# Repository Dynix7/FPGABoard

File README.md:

# FPGABoard
This is a FPGA (Field Programmable Array) board that consists of a iCE40 FPGA, FT2232 Programmer, and IO options. It has 2 PMOD headers (12 pin and 6 pin) along with an programming header and 26 pin header for anything else you want to plug in. On the board it has 3 LEDs and 3 buttons, allowing you to interact with the board without plugging anything in

# Why I Made It
I have a decent amount of experience working with microcontrollers but never any with FPGAs. I also want to learn Verilog which allows you to design circuits using programming, so a FPGA board would be perfect for this use case allowing me to experiment with Verilog and designing circuits while also learning something new.

# Pictures

# BOM

|Name                  |Purpose                        |Quantity|Total Cost (USD)|Link                                                                                                                       |Distributor|
|----------------------|-------------------------------|--------|----------------|---------------------------------------------------------------------------------------------------------------------------|-----------|
|6 Pin Header          |6 Pin PMOD Connector           |        |0.39            |https://www.lcsc.com/product-detail/C2935996.html                                                                          |LCSC       |
|2x6 Pin Header        |12 Pin PMOD Connector          |        |0.74            |https://www.lcsc.com/product-detail/C47326634.html                                                                         |LCSC       |
|2x4 Pin Header        |Programing Header              |        |0.52            |https://www.lcsc.com/product-detail/C7494793.html                                                                          |LCSC       |
|2x13 Pin Female Header|IO Pin Header                  |        |0.32            |https://www.lcsc.com/product-detail/C19268725.html                                                                         |LCSC       |
|Ferrite Bead 60@100   |Power Filtering                |        |0.23            |https://www.lcsc.com/product-detail/C307775.html                                                                           |LCSC       |
|Solder Paste          |Solder Components              |1       |4.79            |https://www.aliexpress.us/item/3256809026940371.html                                                                       |Aliexpress |
|4.7u Capacitors       |Decoupling Capacitors          |        |0.10            |                                                                                                                           |LCSC       |
|12k Resistor          |Resistor                       |        |0.11            |                                                                                                                           |LCSC       |
|2.2k Resistor         |Resistor                       |        |0.13            |                                                                                                                           |LCSC       |
|IS62LV256AL-45ULI     |SRAM for Chip                  |1       |1.84            |https://www.digikey.com/short/70fz9v3d                                                                                     |Digikey    |
|12Mhz Oscillator      |Clock for FPGA and FT2232      |2       |0.87            |https://www.lcsc.com/product-detail/C37635404.html                                                                         |LCSC       |
|93LC66BT-I/OT         |FT2232 Memory                  |        |0.35            |https://www.digikey.com/short/q0nprmz5                                                                                     |Digikey    |
|AP2127K-1.2           |1.2V Voltage Regulator         |        |0.59            |https://www.lcsc.com/product-detail/C151376.html                                                                           |LCSC       |
|AP2127K-3.3           |3.3V Voltage Regulator         |        |0.53            |https://www.lcsc.com/product-detail/C156285.html                                                                           |LCSC       |
|FT2232HPQ             |USB to SPI Chip for programming|1       |8.88            |https://www.lcsc.com/product-detail/C3228692.html                                                                          |LCSC       |
|iCE40HX1K-VQ100       |Main FPGA Chip                 |1       |12.17           |https://www.lcsc.com/product-detail/C1519043.html?lcsc_vid=EwVcU11XEQBXAlBTE1QPVFVTRFELUl0HFAIPUlVTQQMxVlNRQVldU1dRQVFaVDtW|LCSC       |
|Stencil               |For PCB assembly               |1       |7.11            |                                                                                                                           |JLCPCB     |
|PCB                   |PCB for Build                  |5       |12.00           |                                                                                                                           |JLCPCB     |

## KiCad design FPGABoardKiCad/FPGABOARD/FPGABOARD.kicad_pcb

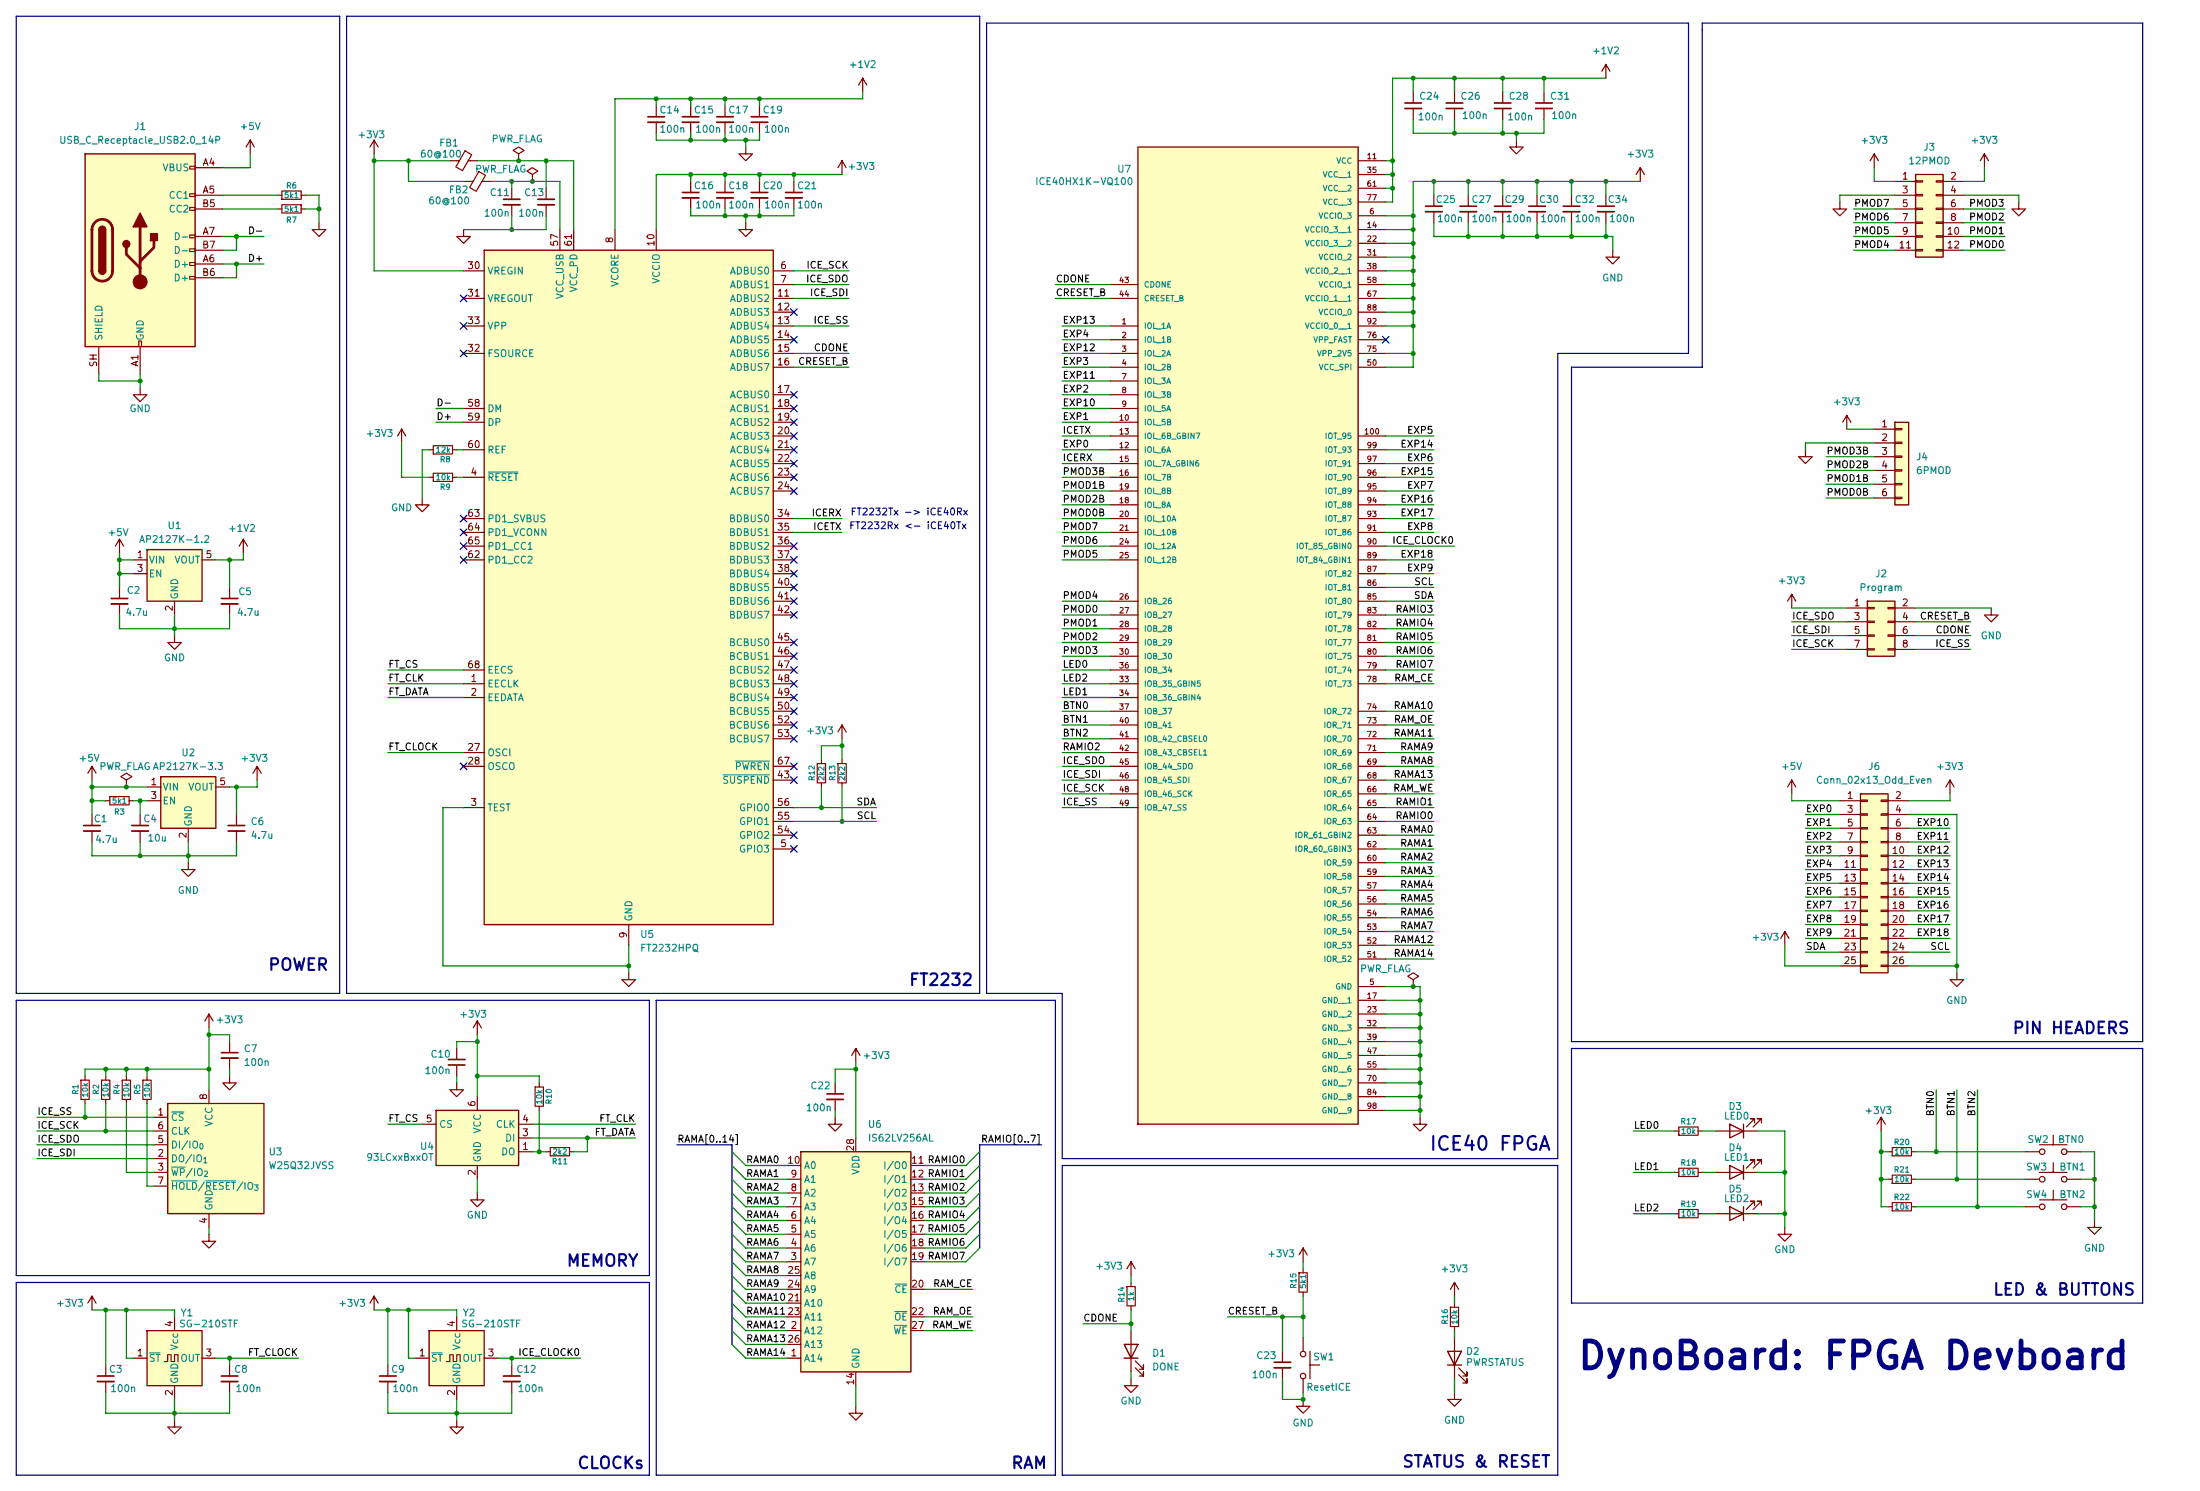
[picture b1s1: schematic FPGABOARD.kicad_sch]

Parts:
C1, C2, C5, C6: 4.7u; C_0603_1608Metric
C3, C7, C8, C9, C10, C11, C12, C13, C23: 100n; C_0603_1608Metric
C4: 10u; C_0603_1608Metric
C14, C15, C16, C17, C18, C19, C20, C21, C22, C24, C25, C26, C27, C28, C29, C30, C31, C32, C34: 100n; C_0603_1608Metric_Pad1.08x0.95mm_HandSolder
D1: DONE; LED_1206_3216Metric
D2: PWRSTATUS; LED_1206_3216Metric
D3: LED0; LED_1206_3216Metric
D4: LED1; LED_1206_3216Metric
D5: LED2; LED_1206_3216Metric
FB1, FB2: 60@100; L_0603_1608Metric
J1: USB_C_Receptacle_USB2.0_14P; USB_C_Receptacle_G-Switch_GT-USB-7010ASV
J2: Program; PinSocket_2x04_P2.54mm_Vertical
J3: 12PMOD; PinSocket_2x06_P2.54mm_Horizontal
J4: 6PMOD; PinSocket_1x06_P2.54mm_Horizontal
J6: Conn_02x13_Odd_Even; PinSocket_2x13_P2.54mm_Vertical
R1, R2, R4, R5, R10, R16, R17, R18, R19, R20, R21, R22: 10k; R_0603_1608Metric
R3, R6, R7, R15: 5k1; R_0603_1608Metric
R8: 12k; R_0603_1608Metric
R9: 10k; R_0603_1608Metric_Pad0.98x0.95mm_HandSolder
R11, R12, R13: 2k2; R_0603_1608Metric
R14: 1k; R_0603_1608Metric
SW1: ResetICE; SW_SPST_PTS647_Sx50
SW2: BTN0; SW_SPST_PTS647_Sx50
SW3: BTN1; SW_SPST_PTS647_Sx50
SW4: BTN2; SW_SPST_PTS647_Sx50
U1: AP2127K-1.2; SOT-23-5_HandSoldering
U2: AP2127K-3.3; SOT-23-5_HandSoldering
U3: W25Q32JVSS; SOIC-8_5.3x5.3mm_P1.27mm
U4: 93LCxxBxxOT; SOT-23-6
U5: FT2232HPQ; VQFN-68-1EP_8x8mm_P0.4mm_EP4.3x4.3mm
U6: IS62LV256AL; SOP-28_8.4x18.16mm_P1.27mm
U7: ICE40HX1K-VQ100; TQFP-100_14x14mm_P0.5mm; PARTREV 3.4
Y1, Y2: SG-210STF; Oscillator_SMD_SeikoEpson_SG210-4Pin_2.5x2.0mm

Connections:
+1V2: C5.1, C14.1, C15.1, C17.1, C19.1, C24.1, C26.1, C28.1, C31.1, U1.5 (VOUT), U5.8 (VCORE), U5.25 (VCORE), U5.44 (VCORE), U5.66 (VCORE), U7.11 (VCC), U7.35 (VCC__1), U7.61 (VCC__2), U7.77 (VCC__3)
+3V3: C3.1, C6.1, C7.1, C9.1, C10.2, C16.1, C18.1, C20.1, C21.1, C22.1, C25.1, C27.1, C29.1, C30.1, C32.1, C34.1, FB1.2, FB2.2, J2.1, J3.1, J3.2, J4.1, J6.2, J6.25, R1.1, R2.1, R4.1, R5.1, R9.1, R10.1, R12.1, R13.1, R14.1, R15.1, R16.1, R20.1, R21.1, R22.1, U2.5 (VOUT), U3.8 (VCC), U4.6 (VCC), U5.10 (VCCIO), U5.26 (VCCIO), U5.30 (VREGIN), U5.39 (VCCIO), U5.51 (VCCIO), U6.28 (VDD), U7.6 (VCCIO_3), U7.14 (VCCIO_3__1), U7.22 (VCCIO_3__2), U7.31 (VCCIO_2), U7.38 (VCCIO_2__1), U7.50 (VCC_SPI), U7.58 (VCCIO_1), U7.67 (VCCIO_1__1), U7.75 (VPP_2V5), U7.88 (VCCIO_0), U7.92 (VCCIO_0__1), Y1.1 (~ST), Y1.4 (Vcc), Y2.1 (~ST), Y2.4 (Vcc)
+5V: C1.1, C2.1, J1.A4 (VBUS), J1.A9 (VBUS), J1.B4 (VBUS), J1.B9 (VBUS), J6.1, R3.1, U1.1 (VIN), U1.3 (EN), U2.1 (VIN)
/BTN0: R20.2, SW2.1, U7.37 (IOB_37)
/BTN1: R21.2, SW3.1, U7.40 (IOB_41)
/BTN2: R22.2, SW4.1, U7.41 (IOB_42_CBSEL0)
/CDONE: D1.2 (A), J2.6, R14.2, U5.15 (ADBUS6), U7.43 (CDONE)
/CRESET_B: C23.1, J2.4, R15.2, SW1.1, U5.16 (ADBUS7), U7.44 (CRESET_B)
/D+: J1.A6 (D+), J1.B6 (D+), U5.59 (DP)
/D-: J1.A7 (D-), J1.B7 (D-), U5.58 (DM)
/EXP0: J6.3, U7.12 (IOL_6A)
/EXP1: J6.5, U7.10 (IOL_5B)
/EXP2: J6.7, U7.8 (IOL_3B)
/EXP3: J6.9, U7.4 (IOL_2B)
/EXP4: J6.11, U7.2 (IOL_1B)
/EXP5: J6.13, U7.100 (IOT_95)
/EXP6: J6.15, U7.97 (IOT_91)
/EXP7: J6.17, U7.95 (IOT_89)
/EXP8: J6.19, U7.91 (IOT_86)
/EXP9: J6.21, U7.87 (IOT_82)
/EXP10: J6.6, U7.9 (IOL_5A)
/EXP11: J6.8, U7.7 (IOL_3A)
/EXP12: J6.10, U7.3 (IOL_2A)
/EXP13: J6.12, U7.1 (IOL_1A)
/EXP14: J6.14, U7.99 (IOT_93)
/EXP15: J6.16, U7.96 (IOT_90)
/EXP16: J6.18, U7.94 (IOT_88)
/EXP17: J6.20, U7.93 (IOT_87)
/EXP18: J6.22, U7.89 (IOT_84_GBIN1)
/FT_CLK: U4.4 (CLK), U5.1 (EECLK)
/FT_CLOCK: C8.1, U5.27 (OSCI), Y1.3 (OUT)
/FT_CS: U4.5 (CS), U5.68 (EECS)
/FT_DATA: R11.2, U4.3 (DI), U5.2 (EEDATA)
/ICERX: U5.34 (BDBUS0), U7.15 (IOL_7A_GBIN6)
/ICETX: U5.35 (BDBUS1), U7.13 (IOL_6B_GBIN7)
/ICE_CLOCK0: C12.1, U7.90 (IOT_85_GBIN0), Y2.3 (OUT)
/ICE_SCK: J2.7, R2.2, U3.6 (CLK), U5.6 (ADBUS0), U7.48 (IOB_46_SCK)
/ICE_SDI: J2.5, U3.2 (DO/IO_{1}), U5.11 (ADBUS2), U7.46 (IOB_45_SDI)
/ICE_SDO: J2.3, U3.5 (DI/IO_{0}), U5.7 (ADBUS1), U7.45 (IOB_44_SDO)
/ICE_SS: J2.8, R1.2, U3.1 (~CS), U5.13 (ADBUS4), U7.49 (IOB_47_SS)
/LED0: R17.1, U7.36 (IOB_34)
/LED1: R18.1, U7.34 (IOB_36_GBIN4)
/LED2: R19.1, U7.33 (IOB_35_GBIN5)
/PMOD0: J3.12, U7.27 (IOB_27)
/PMOD0B: J4.6, U7.20 (IOL_10A)
/PMOD1: J3.10, U7.28 (IOB_28)
/PMOD1B: J4.5, U7.19 (IOL_8B)
/PMOD2: J3.8, U7.29 (IOB_29)
/PMOD2B: J4.4, U7.18 (IOL_8A)
/PMOD3: J3.6, U7.30 (IOB_30)
/PMOD3B: J4.3, U7.16 (IOL_7B)
/PMOD4: J3.11, U7.26 (IOB_26)
/PMOD5: J3.9, U7.25 (IOL_12B)
/PMOD6: J3.7, U7.24 (IOL_12A)
/PMOD7: J3.5, U7.21 (IOL_10B)
/RAMA0: U6.10 (A0), U7.63 (IOR_61_GBIN2)
/RAMA1: U6.9 (A1), U7.62 (IOR_60_GBIN3)
/RAMA2: U6.8 (A2), U7.60 (IOR_59)
/RAMA3: U6.7 (A3), U7.59 (IOR_58)
/RAMA4: U6.6 (A4), U7.57 (IOR_57)
/RAMA5: U6.5 (A5), U7.56 (IOR_56)
/RAMA6: U6.4 (A6), U7.54 (IOR_55)
/RAMA7: U6.3 (A7), U7.53 (IOR_54)
/RAMA8: U6.25 (A8), U7.69 (IOR_68)
/RAMA9: U6.24 (A9), U7.71 (IOR_69)
/RAMA10: U6.21 (A10), U7.74 (IOR_72)
/RAMA11: U6.23 (A11), U7.72 (IOR_70)
/RAMA12: U6.2 (A12), U7.52 (IOR_53)
/RAMA13: U6.26 (A13), U7.68 (IOR_67)
/RAMA14: U6.1 (A14), U7.51 (IOR_52)
/RAMIO0: U6.11 (I/O0), U7.64 (IOR_63)
/RAMIO1: U6.12 (I/O1), U7.65 (IOR_64)
/RAMIO2: U6.13 (I/O2), U7.42 (IOB_43_CBSEL1)
/RAMIO3: U6.15 (I/O3), U7.83 (IOT_79)
/RAMIO4: U6.16 (I/O4), U7.82 (IOT_78)
/RAMIO5: U6.17 (I/O5), U7.81 (IOT_77)
/RAMIO6: U6.18 (I/O6), U7.80 (IOT_75)
/RAMIO7: U6.19 (I/O7), U7.79 (IOT_74)
/RAM_CE: U6.20 (~CE), U7.78 (IOT_73)
/RAM_OE: U6.22 (~OE), U7.73 (IOR_71)
/RAM_WE: U6.27 (~WE), U7.66 (IOR_65)
/SCL: J6.24, R13.2, U5.55 (GPIO1), U7.86 (IOT_81)
/SDA: J6.23, R12.2, U5.56 (GPIO0), U7.85 (IOT_80)
GND: C1.2, C2.2, C3.2, C4.2, C5.2, C6.2, C7.2, C8.2, C9.2, C10.1, C11.2, C12.2, C13.2, C14.2, C15.2, C16.2, C17.2, C18.2, C19.2, C20.2, C21.2, C22.2, C23.2, C24.2, C25.2, C26.2, C27.2, C28.2, C29.2, C30.2, C31.2, C32.2, C34.2, D1.1 (K), D2.1 (K), D3.1 (K), D4.1 (K), D5.1 (K), J1.A1 (GND), J1.A12 (GND), J1.B1 (GND), J1.B12 (GND), J1.SH (SHIELD), J2.2, J3.3, J3.4, J4.2, J6.4, J6.26, R6.2, R7.1, R8.1, SW1.2, SW2.2, SW3.2, SW4.2, U1.2 (GND), U2.2 (GND), U3.4 (GND), U4.2 (GND), U5.3 (TEST), U5.9 (GND), U5.29 (GND), U5.69 (GND), U6.14 (GND), U7.5 (GND), U7.17 (GND__1), U7.23 (GND__2), U7.32 (GND__3), U7.39 (GND__4), U7.47 (GND__5), U7.55 (GND__6), U7.70 (GND__7), U7.84 (GND__8), U7.98 (GND__9), Y1.2 (GND), Y2.2 (GND)
unnamed: D2.2 (A), R16.2
unnamed: D3.2 (A), R17.2
unnamed: D4.2 (A), R18.2
unnamed: D5.2 (A), R19.2
unnamed: J1.A5 (CC1), R6.1
unnamed: J1.B5 (CC2), R7.2
unnamed: C4.1, R3.2, U2.3 (EN)
unnamed: R5.2, U3.7 (~HOLD/~RESET/IO_{3})
unnamed: R4.2, U3.3 (~WP/IO_{2})
unnamed: R10.2, R11.1, U4.1 (DO)
unnamed: R8.2, U5.60 (REF)
unnamed: C13.1, FB1.1, U5.61 (VCC_PD)
unnamed: C11.1, FB2.1, U5.57 (VCC_USB)
unnamed: R9.2, U5.4 (~RESET)

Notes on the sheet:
RAM
FT2232Rx <- iCE40Tx
FT2232Tx -> iCE40Rx
PIN HEADERS
LED & BUTTONS
FT2232
DynoBoard: FPGA Devboard
CLOCKs
ICE40 FPGA
STATUS & RESET
MEMORY
POWER

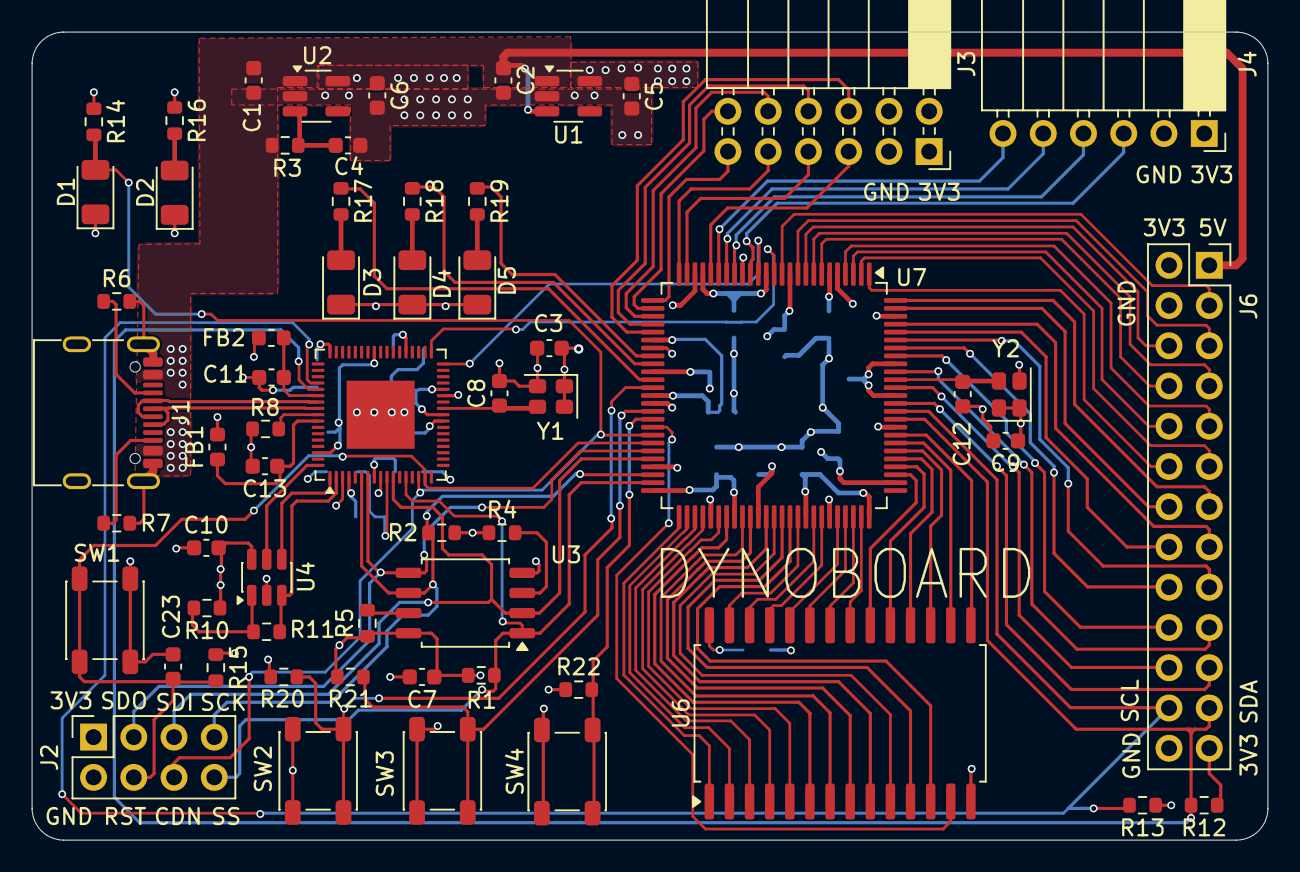
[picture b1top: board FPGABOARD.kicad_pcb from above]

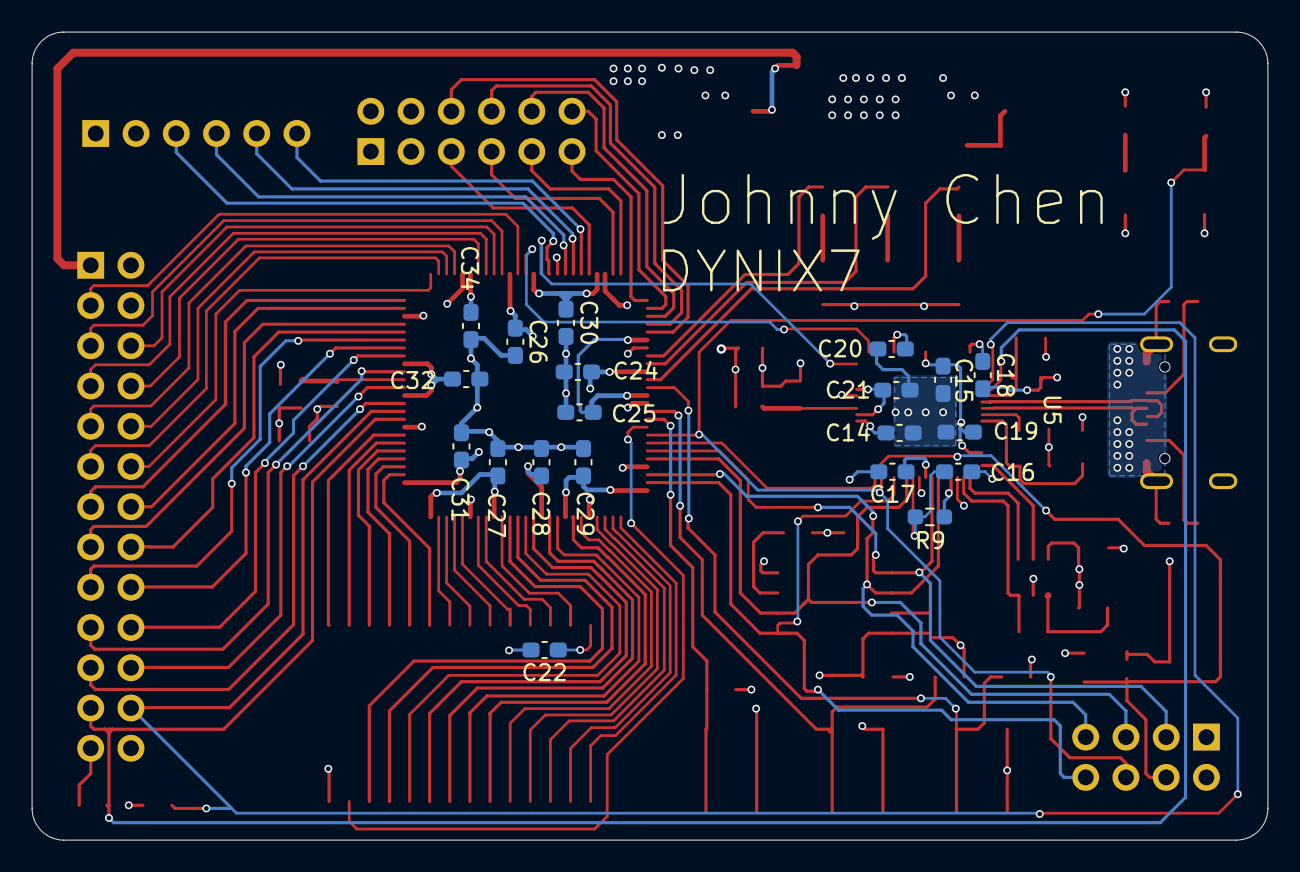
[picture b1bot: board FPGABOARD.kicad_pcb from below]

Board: 4 copper layers, 78.0 x 51.0 mm, 80 parts (20 on the bottom side), 98 nets.

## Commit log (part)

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2026-04-08 Start Schematic
2026-04-09 Schematic Work
2026-04-10 FT2232 Wiring
2026-04-10 Update IO
2026-04-13 Some placements
2026-04-15 More pcb work
2026-04-16 More placements
2026-04-17 Finished placements mostly
2026-04-19 Finsished up Header and Memory routing
2026-04-19 Minor wiring change
2026-04-19 Add programing header
2026-04-19 Changed to 0603
2026-04-20 Images
2026-04-20 image update
2026-04-20 update production file
2026-04-23 add bom
